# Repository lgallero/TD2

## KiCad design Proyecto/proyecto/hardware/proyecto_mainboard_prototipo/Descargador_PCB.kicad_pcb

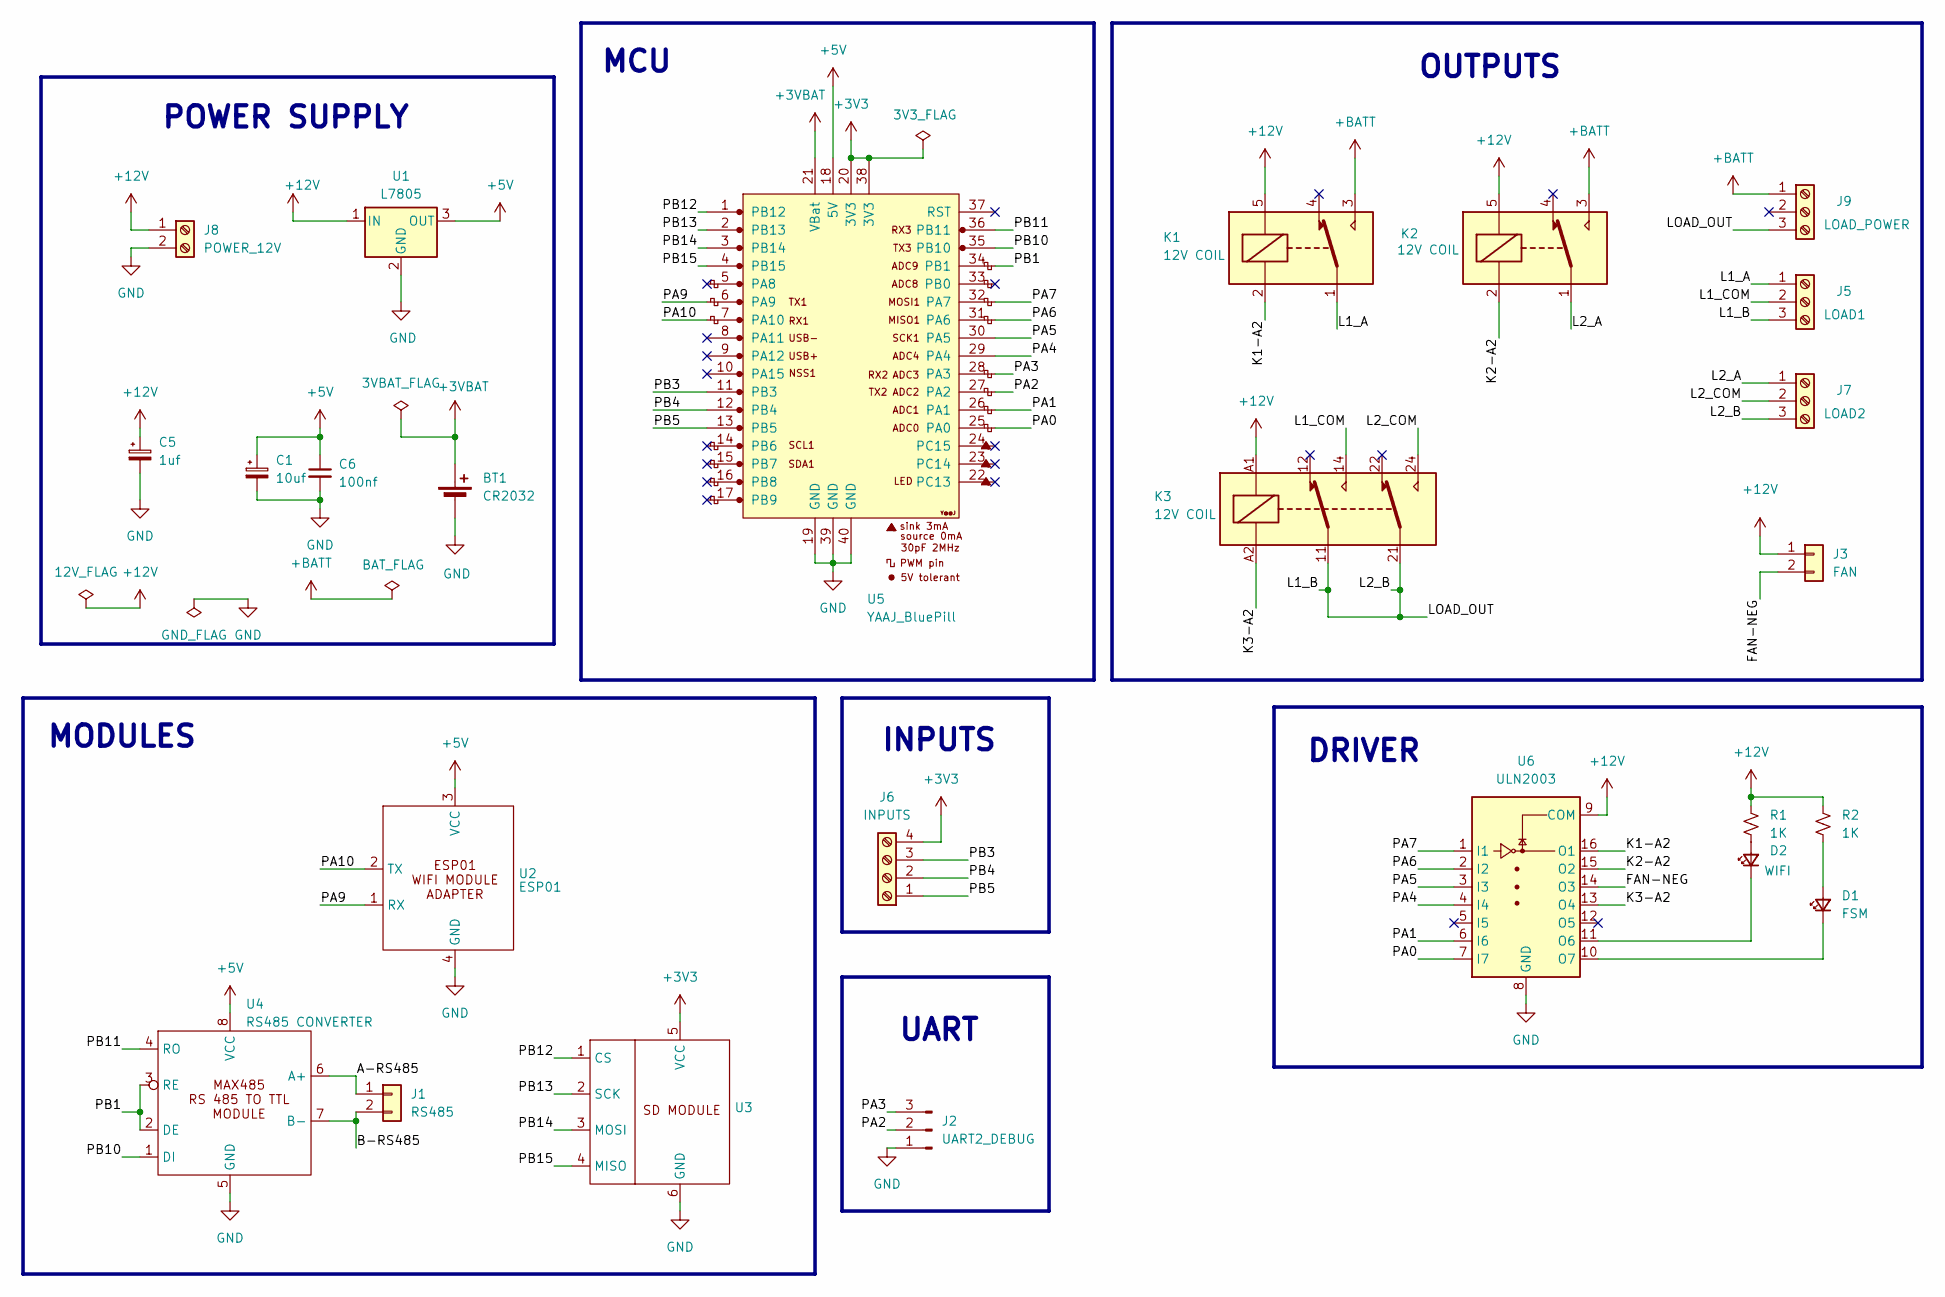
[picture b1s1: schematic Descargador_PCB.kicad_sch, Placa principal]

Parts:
BT1: CR2032; BatteryHolder_MYOUNG_BS-07-A1BJ001_CR2032
C1: 10uf; CP_Radial_D6.3mm_P2.50mm
C5: 1uf; CP_Radial_D6.3mm_P2.50mm
C6: 100nf; C_Disc_D4.3mm_W1.9mm_P5.00mm
D1: FSM; LED_D3.0mm
D2: WIFI; LED_D3.0mm
J1: RS485; Molex_KK-254_AE-6410-02A_1x02_P2.54mm_Vertical
J2: UART2_DEBUG; PinHeader_1x03_P2.54mm_Vertical
J3: FAN; Molex_KK-254_AE-6410-02A_1x02_P2.54mm_Vertical
J5: LOAD1; TerminalBlock_Phoenix_MKDS-1,5-3-5.08_1x03_P5.08mm_Horizont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
J6: INPUTS; TerminalBlock_Phoenix_MKDS-1,5-4_1x04_P5.00mm_Horizontal
J7: LOAD2; TerminalBlock_Phoenix_MKDS-1,5-3-5.08_1x03_P5.08mm_Horizont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
J8: POWER_12V; TerminalBlock_Phoenix_MKDS-1,5-2_1x02_P5.00mm_Horizontal
J9: LOAD_POWER; TerminalBlock_Phoenix_MKDS-1,5-3-5.08_1x03_P5.08mm_Horizont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
K1, K2: 12V COIL; Relay_SPDT_SANYOU_SRD_Series_Form_C
K3: 12V COIL; Relay_DPDT_Finder_40.52
R1, R2: 1K; R_Axial_DIN0207_L6.3mm_D2.5mm_P10.16mm_Horizontal
U1: L7805; TO-220-3_Vertical
U2: ESP01; ESP01_adapter_4pin_P2.54
U3: SD MODULE; PinSocket_1x06_P2.54mm_Vertical
U4: RS485 CONVERTER; RS485_module_headers_P2.54
U5: YAAJ_BluePill; YAAJ_BluePill_1
U6: ULN2003; DIP-16_W7.62mm_Socket

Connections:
+3V3: J6.4, U3.5 (VCC), U5.20 (3V3), U5.38 (3V3)
+3VBAT: BT1.1 (+), U5.21 (VBat)
+5V: C1.1, C6.1, U1.3 (OUT), U2.3 (VCC), U4.8 (VCC), U5.18 (5V)
+12V: C5.1, J3.1, J8.1, K1.5, K2.5, K3.A1, R1.1, R2.1, U1.1 (IN), U6.9 (COM)
+BATT: J9.1, K1.3, K2.3
/A-RS485: J1.1, U4.6 (A+)
/B-RS485: J1.2, U4.7 (B-)
/FAN-NEG: J3.2, U6.14 (O3)
/K1-A2: K1.2, U6.16 (O1)
/K2-A2: K2.2, U6.15 (O2)
/K3-A2: K3.A2, U6.13 (O4)
/L1_A: J5.1, K1.1
/L1_B: J5.3, J7.3, J9.3, K3.11, K3.21
/L1_COM: J5.2, K3.14
/L2_A: J7.1, K2.1
/L2_COM: J7.2, K3.24
/PA0: U5.25 (PA0), U6.7 (I7)
/PA1: U5.26 (PA1), U6.6 (I6)
/PA2: J2.2, U5.27 (PA2)
/PA3: J2.3, U5.28 (PA3)
/PA4: U5.29 (PA4), U6.4 (I4)
/PA5: U5.30 (PA5), U6.3 (I3)
/PA6: U5.31 (PA6), U6.2 (I2)
/PA7: U5.32 (PA7), U6.1 (I1)
/PA9: U2.1 (RX), U5.6 (PA9)
/PA10: U2.2 (TX), U5.7 (PA10)
/PB1: U4.2 (DE), U4.3 (RE), U5.34 (PB1)
/PB3: J6.3, U5.11 (PB3)
/PB4: J6.2, U5.12 (PB4)
/PB5: J6.1, U5.13 (PB5)
/PB10: U4.1 (DI), U5.35 (PB10)
/PB11: U4.4 (RO), U5.36 (PB11)
/PB12: U3.1 (CS), U5.1 (PB12)
/PB13: U3.2 (SCK), U5.2 (PB13)
/PB14: U3.3 (MOSI), U5.3 (PB14)
/PB15: U3.4 (MISO), U5.4 (PB15)
GND: BT1.2 (-), C1.2, C5.2, C6.2, J2.1, J8.2, U1.2 (GND), U2.4 (GND), U3.6 (GND), U4.5 (GND), U5.19 (GND), U5.39 (GND), U5.40 (GND), U6.8 (GND)
unnamed: D1.2 (A), R2.2
unnamed: D1.1 (K), U6.10 (O7)
unnamed: D2.2 (A), R1.2
unnamed: D2.1 (K), U6.11 (O6)

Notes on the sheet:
UART
POWER SUPPLY
MCU
INPUTS
DRIVER
MODULES
OUTPUTS

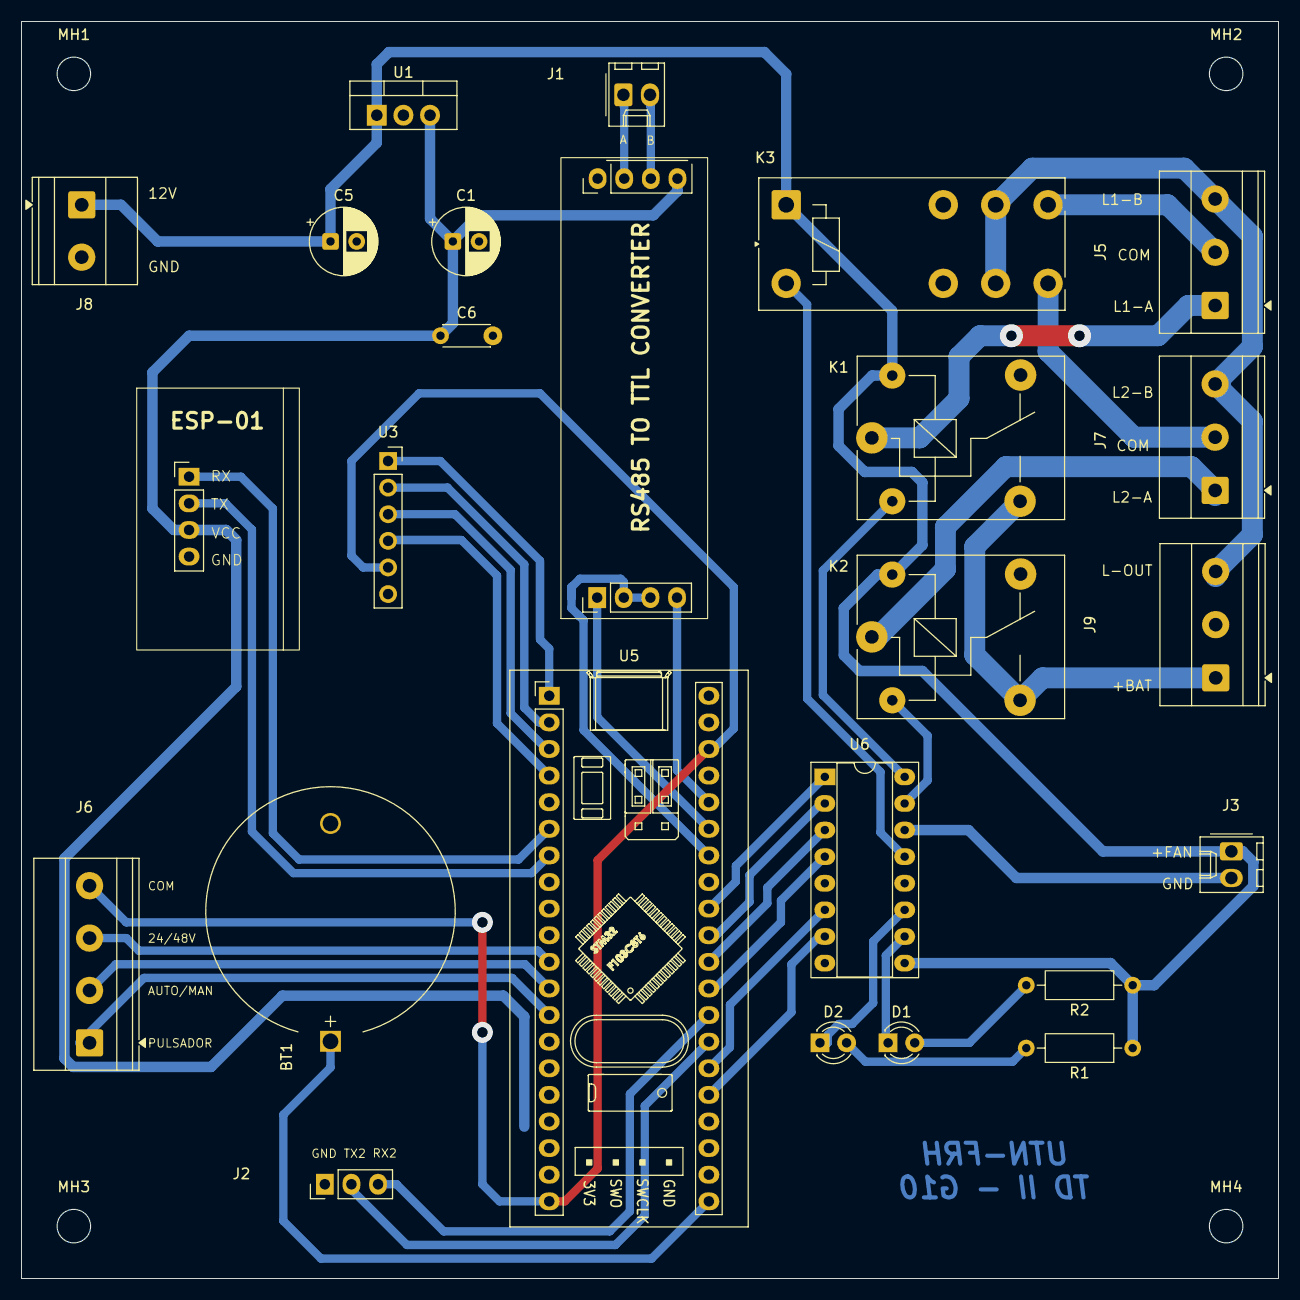
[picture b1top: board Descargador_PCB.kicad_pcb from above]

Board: 2 copper layers, 120.0 x 120.0 mm, 29 parts (0 on the bottom side), 41 nets.

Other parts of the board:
MH1, MH2, MH3, MH4: M3_3.2mm; MountingHole_3.2mm_M3_DIN965

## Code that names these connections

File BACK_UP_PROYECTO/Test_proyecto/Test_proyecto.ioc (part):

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Mcu.Name=STM32F103C(8-B)Tx
Mcu.Package=LQFP48
Mcu.UserName=STM32F103C8Tx
PA0-WKUP.GPIOParameters=GPIO_Label
PA0-WKUP.GPIO_Label=FSM_STATE
PA0-WKUP.Signal=GPIO_Output
PA1.GPIOParameters=GPIO_Label
PA1.GPIO_Label=WIFI_STATE
PA1.Signal=GPIO_Output
PA10.Mode=Asynchronous
PA10.Signal=USART1_RX
PA13.Mode=Serial_Wire
PA13.Signal=SYS_JTMS-SWDIO
PA14.Mode=Serial_Wire
PA14.Signal=SYS_JTCK-SWCLK
PA2.Mode=Asynchronous
PA2.Signal=USART2_TX
PA3.Mode=Asynchronous
PA3.Signal=USART2_RX
PA4.GPIOParameters=GPIO_Label
PA4.GPIO_Label=OUT_24_48V
PA4.Signal=GPIO_Output
PA5.GPIOParameters=GPIO_Label
PA5.GPIO_Label=FAN_OUT
PA5.Signal=GPIO_Output
PA6.GPIOParameters=GPIO_Label
PA6.GPIO_Label=LOAD2
PA6.Signal=GPIO_Output
PA7.GPIOParameters=GPIO_Label
PA7.GPIO_Label=LOAD1
PA7.Signal=GPIO_Output
PA9.Mode=Asynchronous
PA9.Signal=USART1_TX
PB1.GPIOParameters=GPIO_Label
PB1.GPIO_Label=RS485_DE
PB1.Signal=GPIO_Output
PB10.Mode=Asynchronous
PB10.Signal=USART3_TX
PB11.Mode=Asynchronous
PB11.Signal=USART3_RX
PB3.GPIOParameters=GPIO_PuPd,GPIO_Label
PB3.GPIO_Label=TENSION_24_48
PB3.GPIO_PuPd=GPIO_PULLDOWN
PB3.Signal=GPIO_Input
PB4.GPIOParameters=GPIO_PuPd,GPIO_Label
PB4.GPIO_Label=AUTO_MANUAL
PB4.GPIO_PuPd=GPIO_PULLDOWN
PB4.Signal=GPIO_Input
PB5.GPIOParameters=GPIO_PuPd,GPIO_Label
PB5.GPIO_Label=PULSADOR
PB5.GPIO_PuPd=GPIO_PULLDOWN
PB5.Signal=GPXTI5
PC13-TAMPER-RTC.GPIOParameters=GPIO_Label
PC13-TAMPER-RTC.GPIO_Label=LED_BP
PC13-TAMPER-RTC.Signal=GPIO_Output
PC14-OSC32_IN.Mode=LSE-External-Oscillator
PC14-OSC32_IN.Signal=RCC_OSC32_IN
PC15-OSC32_OUT.Mode=LSE-External-Oscillator
PC15-OSC32_OUT.Signal=RCC_OSC32_OUT
PD0-OSC_IN.Mode=HSE-External-Oscillator
PD0-OSC_IN.Signal=RCC_OSC_IN
PD1-OSC_OUT.Mode=HSE-External-Oscillator
PD1-OSC_OUT.Signal=RCC_OSC_OUT
board=custom
